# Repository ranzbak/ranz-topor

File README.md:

# topor — topological curved-trace router for KiCad

topor routes PCB connections as smooth, taut traces (straight segments joined by tangent arcs),
using topological routing: first decide *which side of every obstacle* a wire passes, then pull
each wire tight. It respects KiCad's design rules and checks its output with KiCad's own DRC.

Engine in Rust (`engine/`), packaged as a Python wheel; KiCad 10 plugin in `plugin/` (IPC API);
test and benchmark harness in `harness/`. Linux only for now.

## Status (version 0.4.0, milestone M4b: the plugin)

| Works now, from inside KiCad 10 | Comes in 0.5.0 (milestone M4a: the engine) |
|---|---|
| **Topor: route** button: pre-flight findings (code, cause, fix), options, progress with Cancel, before/after preview, **Accept = one undo step for the routes** (plus one for the zone refill) / Reject = nothing changed | private-badge-b n/n routed, 0 router DRC, ≤ 10 min (now 148/n in 60 s) |
| Whole board or a selection (between / touching selected footprints); existing copper kept, or ripped and re-routed; locked copper respected | priorities used for routing order (`@N` markers, `topor_pN` net classes, `[nets] priority` — computed and reported now) |
| Self-documenting `topor.toml` per project, generated [reference](docs/user/configuration.md); every finding names the KiCad menu or the key to change | pad exit stubs for fine pitch, same-net T-junctions, via rules from the board setup, bounded via relaxation, layer costs |
| Result verified by `kicad-cli` DRC on a copy before you decide; report folder (report, preview, DRC, log) per run | engine-side `do_not_touch` / `ignore_pads` options (applied by the plugin's scope now) |
| eprom-to-kernal 27/27 and wiccon-2023 62/62 routed, `routing_new 0`, `unconnected 0` (headless, judged by `kicad-cli`) | eprom / wiccon not worse than now |

The plugin needs a live GUI test before the 0.4.0 gate closes:
[docs/user/gui-test-checklist.md](docs/user/gui-test-checklist.md). Known limits:
[operate.md → Limitations](docs/user/operate.md#limitations).

## Topological core (branch `topor-topo`, in development)

A new engine core, written after TopoR's approach: the board is projected into one triangulation of all pads,
holes, keepouts, copper graphics and the outline; every connection is searched there as a topological path
(which side of each obstacle it passes), its net growing as a tree (a connection may end on a pad or a branch
point of copper it joins, including through-pad junctions); layers are assigned afterwards (Polubasov's via
minimisation), then rip-up and reroute, via reduction, and finally the drawing pulls each wire taut and checks
it against KiCad's rules. Plane pads get a stub and a via into their pour before any of this, so the planner
routes around them (a pour that fills only the pad's own layers gets a track alone into the fill); a pad that
no stub can serve is joined to its net's copper by a signal connection instead; pour pieces the routed copper
cuts off are stitched back with island vias or pad stubs.

What works on this branch:

- graded social factors instead of hard thresholds, each with a weight in `topor.toml [factors]` and a line in
  the run report: via_squeeze, junction_angle, branch, blocks_pad, squeeze, congestion, ignored_rule, and more
  ([factor reference](docs/dev/factors.md));
- keepouts: track keepouts per layer, via keepouts on any copper layer (a through via spans them all), pour
  keepouts in the fill estimate; copper graphics are obstacles on their layer;
- pour-island stitching after routing, and KiCad's minimum connection width respected by vias and stubs;
- layer-aware crossings: the search knows the layers each crossed trace is held to and does not cross where
  no layer assignment can separate the two (`[search] crossing_vias = "via"` also prices the implied via;
  off by default, the crossing factor stands for it);
- net-tree junctions in the layer assignment (two layers): a T junction is one layer domain (Polubasov's tee
  rule: two arms on one layer, the via on the third), and a via next to a junction stands at the junction;
  the junction angle price follows the Steiner-tree length bound (`junction_angle`, ψ curve, 0 from 120°);
- fuse after drawing: a trace that leaves a branch point or a pad right beside another trace of its net
  starts on that trace's copper where the two part (one copper, a T there), when that is cheaper by length
  and junction angle (and, in the octilinear style, by the drawing's own bend and any-angle prices: the link
  is an elbow or Z at 0/45/90 degrees where it fits) and keeps every clearance (`[search] fuse_branches`, on
  by default);
- the drawing's exact path has no out-and-back track pieces at its joints any more.

The board ladder at commit `121e3eb` (headless, `tools/route_board.sh`, judged by `kicad-cli` DRC after a zone
refill; "unconnected" counts DRC unconnected items, the hand-routed board's own count in brackets).
`private-badge-b` in this and the tables below is a 2-layer badge (a few hundred connections, written n, USB-C, arcs) whose design files
are not public; its rows stay as measurements, the public stand-in for new runs is esp-rust-board:

| Board | Routed | Unconnected (hand) | New routing DRC errors | Vias |
|---|---|---|---|---|
| eprom-to-kernal | 27/27 | 0 (0) | 0 | 0 |
| wiccon-2023 | 60/60 | 0 (0) | 0 | 23 |
| private-badge-b | 189/n | 47 (4) | 0 | 116 |
| qmtech | 346/426 | 85 (0) | 0 | 195 |

### The topological core inside KiCad (K1)

The **Topor: route** button runs this core in KiCad 10: pre-flight findings (pads inside track keepouts), a progress dialog that names the stage and round and shows router time and
total time (`[run] timeout_s` is now 600 s, an emergency stop; the `[optimize]` work caps end a run), Cancel at any
time, a preview with the open ratsnest in blue and a yellow dot at each rule violation the engine reports (while the loop runs, smaller dots at the plan's predicted errors), findings after routing (unrouted connections by reason, pour
islands and stitches, via squeeze, necking, ignored rules, ...; [operate.md](docs/user/operate.md#findings-after-routing)),
Accept (routes = one undo step, zone refill = a second). Every `topor.toml` setting the core reads reaches it (before K1 the `[optimize]`,
`[factors]` and the other core settings were dropped as "since 0.5.0"); settings of the classic engine say so in
the [reference](docs/user/configuration.md).

Live test, automated: `tools/gui_e2e.sh <board> <out_dir> --from-hand [--harness <metrics.json>]` drives KiCad 10
on a nested X display (Xephyr) with a separate KiCad home, never yours, opens a copy of the hand-routed board,
routes with *Rip up and re-route*, accepts, checks one Ctrl+Z restores the board, saves and judges the result with
KiCad's DRC ([gui-test-checklist.md](docs/user/gui-test-checklist.md#automated-run)). Plugin in KiCad vs the
headless harness on the same board (engine at K1):

| Board | Live plugin: routed / unconnected / routing_new / vias | Harness | Same? |
|---|---|---|---|
| wiccon-2023 | 60/60 / 0 / 0 / 23 | 60/60 / 0 / 0 / 23 | yes |
| private-badge-b | 184/n / 52 / 0 / 110 | 189/n / 47 / 0 / 116 | no: the copper-graphics polygons differ by < 0.5 µm (both contain KiCad's copper); the plugin's engine input with the harness's polygons routes 189/116 |
| qmtech | 349/426 / 84 / 0 / 206 | 346/426 / 85 / 0 / 195 | no: the net numbering differs (KiCad's API has no net codes, the plugin numbers nets by sorted name); the plugin's engine input renumbered with pcbnew's codes routes 346/195 |

Every other part of the engine input is now identical between the plugin and the harness (rules, widths, net
classes and priorities, pads, pours, zone connections, keepouts, teardrops); the remaining differences are the
router's sensitivity to the copper-graphics vertices and to the net numbering, not plugin errors. The ladder above
is unchanged by K1 (eprom 27/27, wiccon 60/60, private-badge-b 189/n, qmtech 346/426, routing_new 0).

### Iterations like TopoR: "Routes stable", OK, best of N runs (M-B0)

(Since M0 this whole-route cycle loop is `[optimize] loop = "cycles"`; the default is TopoR's loop on the topology,
see *Defaults = the TopoR method (M0)* below.) A run no longer stops after a fixed four rounds. Like TopoR it keeps iterating whole-route cycles: every cycle
routes the board again with the passages the drawing found too small lowered and with fluctuating factor weights
(Polubasov 2010) whose width starts wide, narrows every cycle and widens again when the run is stuck with
connections still open (annealing with reheating; `[optimize] fluctuation`, `fluctuation_narrowing`,
`fluctuation_stuck`, `fluctuation_reheat`). Every cycle's variants are pour-stitched and judged (a pour piece left
cut off counts as an error). When the best result gains less than `stable_gain_pct` over `stable_window` cycles the
routes are *stable* (TopoR 6.3 manual p. 73: "Autorouting may be stopped"; not before level 5–10): the progress
dialog says **Routes stable**; its two buttons stay **Accept** (stop and keep the best result so far, exactly the
board shown) and **Cancel** (stop at once, take nothing: the board stays as it was). With the dialog the run keeps
iterating for marginal gains until Accept / Cancel
(user 2026-11-16: "don't stop on stable"; `finish_when_stable = true` makes it finish at stable by itself,
`finish_patience`), and headless runs stop at stable. `[optimize] runs` (default 5) seeded runs go on in
parallel on the engine's threads and the best by the pick (errors, vias, length) is offered; `[optimize] rounds` (30) is only a
safety cap and `[run] timeout_s` (600 s) the emergency stop: runs on large boards (private-badge-b, qmtech with runs = 5) may hit it
and keep the best result so far (`TIME_BUDGET_HIT`).

Scorecard (KiCad DRC after a refill; connected % of KiCad's own input count, default run and median [range] of
seeds 1–5; `harness/scorecard.py`):

| Board | Before (fixed 4 rounds) | M-B0 (best of 5, until stable) | Router time before → after |
|---|---|---|---|
| eprom-to-kernal | 100 / 100 | 100 / 100 | 0.3 s → 2 s |
| wiccon-2023 | 100 / 100 [98.2–100] | 100 / 100 [100–100] | 1 s → 27 s |
| private-badge-b | 77.6 / 76.2 [74.3–78.6] | 80.5 / 79.5 [77.1–80.5] | 53 s → 442 s |
| qmtech | 79.6 / 78.9 [77.5–79.9] | 81.5 / 81.5 [80.6–83.2] | 174 s → 1014 s |

The defaults are provisional; their re-measurement with the M-B1 objective was skipped (user 2026-11-07: next
stage first).

Known limits: the complex boards (bornhack2026, hackerhotel2027, tanmatsu) are not on the ladder yet;
differential pairs are routed coupled but not length- or skew-tuned (D7, below); branching is not complete (the fuse moves copper after drawing but the
planner still reserves room for both traces; re-attaching after changes, junction relaxation toward the
Fermat point, vias as junctions and new branch points are open; the tee rule is two-layer only; a few
side-by-side pairs of one net remain, mostly at adjacent pins of one net and twin plane stubs); pour islands
are stitched afterwards, not prevented; results on the larger rungs move by a few connections with small
changes elsewhere on the board (rip-up order).

### Never drop (M-B1): violations instead of open connections

Like TopoR, a connection is no longer dropped when its drawing finds no legal geometry (a gap too narrow when
drawn, a via without a free site, a crossing that cannot be layered, a branch meeting its trace on another layer).
It stays in the router and is drawn anyway on its least violating geometry (the drawing's attempts, the exact path
with the clearance relaxed by the least amount that gives one, the funnels before the repair; a via goes to its
least violating site). Every rule it breaks is priced very high by the graded `violation` factor (1000 mm per
violation plus 1000 mm per 0.01 mm² of depth × length) and reported with its place, type and cause
(`VIOLATIONS` finding, `violations` in result.json). The best result counts errors first — connections with
violations plus connections without copper ("a design-rule violation cannot be compensated by any reduction of
wire length", Polubasov 2010) — then the least length + 25 mm per via + necking (`[optimize] pick = best`: necking = `neck_mm_per_mm2` x the copper drawn narrower than its net class width, in mm2, + `neck_via_mm` per via smaller than the class via; both defaults are guesses), then fewest shrinkages (`errors_weighted` = the old length + 25 mm per via without necking); "Routes stable" and the best of N see
the same count. The violating copper is written to the board; `[optimize] allow_violations = false` keeps the
legal-only output (such connections stay unrouted, as before). The topological core takes no DRC feedback, so the
plugin judges the result with one DRC round.

Scorecard at the defaults (best of 5 runs, measurement runs cut at 600 s of router time; default run and median
[range] of seeds 1–5; `harness/scorecard.py`, KiCad DRC after a refill):

| Board | Connected % M-B0 | Connected % M-B1 | Total length % of hand | Engine violations (connections) | Router time |
|---|---|---|---|---|---|
| eprom-to-kernal | 100 / 100 | 100 / 100 | 95 | 0 | 2 s |
| wiccon-2023 | 100 / 100 | 100 / 100 [100–100] | 89 / 88 | 0 | 24 s |
| private-badge-b | 80.5 / 79.5 [77.1–80.5] | 92.4 / 91.0 [90.0–91.4] | 62 / 63 | 236–385 (33–41) | 600 s (cut, all 6) |
| qmtech | 81.5 / 81.5 [80.6–83.2] | 91.4 / 91.6 [90.9–93.3] | 96 / 96 | 445–911 (47–58) | 600 s (cut, all 6) |

The violations are many and some are bad (copper over foreign pads and traces, `short` about half of them): the
drawing still realises a plan whose passages are too narrow or whose crossings are on one layer. Removing them
where they arise — the drawing failure fed back to the planner as a local cut, the crossing rules applied in the
topology — is the next stage (M-B2).

### Failures feed back locally; crossing rules in the planner (M-B2)

A cycle now feeds what went wrong back to the next one *where it happened*, and the planner removes the
crossing patterns that force violations while change is still cheap:

- **Local, fading history.** A violation puts history (a price for that connection only) on the passes of its
  trace near the place, weighted by the distance (1 on it, falling smoothly), not on the whole trace (Dr. CU,
  IEEE TCAD 2020, §IV-C: history only on "the intervals with violations"); a via without a site prices only the
  passages around its interval. Everything carried over fades by `[optimize] history_fade` (0.5) per cycle, and the
  present price of an over-full passage is kept level with the largest history so history cannot dominate
  (BoxRouter 2.0, p. 32:8–9). A passage the drawing found too narrow gets a lowered room (a cut, Haas 2026
  §VI-E); when a cycle comes out worse than the best, the cuts turn into a price (`[optimize] soft_cuts`). The
  drawing's rescue rips blocking traces by a graded price instead of a count, and the traces whose via count rose
  are rerouted first (Polubasov 2010).
- **Crossing rules** (`[optimize] crossing_rules`; `engine/src/topo/xrules.rs`): a trace of another net that wraps
  around a connection's terminal pad (a clinch or half-loop at a terminal, Luzin & Popov 2012 pp. 116–118 — the
  user's qmtech ADV7511 → U4 header case), two traces crossing twice (Luzin 2013 Fig. 16) and a crossing whose
  stretches are both held to one layer (Polubasov 2001) are re-planned pairwise — the terminal's trace first, the
  other one laid on the other side — before and after the rip-up, kept when the plan scores better. The planner's
  score counts crossings that cannot be layered as predicted violations.
- The `VIOLATIONS` finding groups what is left by origin: *pad exit* (a neighbour pin of the connection's own part —
  necking and pad exits, planned in M-C), via without a site, crossing, other copper in a narrow passage, static.

Scorecard (same setup as M-B1: best of 5 runs, cut at 600 s of router time; default / median [range] of seeds 1–5):

| Board | Connected % M-B1 | Connected % M-B2 | Engine violations M-B1 → M-B2 (connections) | shorts | Runs cut at 600 s |
|---|---|---|---|---|---|
| eprom-to-kernal | 100 / 100 | 100 / 100 | 0 → 0 | 0 | 0 / 6 |
| wiccon-2023 | 100 / 100 | 100 / 100 [100–100] | 0 → 0 | 0 | 0 / 6 |
| private-badge-b | 92.4 / 91.0 [90.0–91.4] | 90.0 / 91.0 [90.5–92.4] | 236–385 (29–38) → 95–176 (21–25) | 108–177 → 25–74 | 6 → 0 / 6 |
| qmtech | 91.4 / 91.6 [90.9–93.3] | 91.8 / 91.8 [91.1–92.6] | 445–911 (49–58) → 139–280 (32–40) | 234–613 → 35–154 | 6 → 6 / 6 |

Per cycle the errors now fall over the first cycles (median over all runs, private-badge-b 56.5 → 49 → 47.5 → 45;
qmtech 94 → 77.5 → 80.5 → 77 → 75); before, the violations of the later cycles grew (private-badge-b median 240 → 446).
On private-badge-b the default run's 5 more unconnected items are GND pour joins after the refill (stub and zone
pieces), not signal connections: the engine routes 222 of n in every run. On qmtech about 40 % of what is left
is at pad exits (M-C). Still open: the crossing rules leave traces of net trees with branch points alone, and a
trace drawn by force can still run over other copper for a millimetre or two.

### Widths, pad exits and via room decided in the plan (M-C)

The planner now decides what the drawing used to find out the hard way (TopoR's way: decide while change is cheap):

- **Pad exits.** A trace next to its own pad needs half its width plus the clearance to the next pin (the drawing's
  packer model); before, the one-plane routing counted no room at all there and planned exits through the 0.2 mm
  gap between fine-pitch pins, which the drawing then clipped (engine test `topo_mc`).
- **Width in the one-plane routing.** Every pass carries a width: the net width, or the minimum width (KiCad minimum
  track width / custom-rule minimum) where the passage is a bottleneck or the pad exit is too tight (TopoR 6.3
  manual p. 56: the minimum width "in bottlenecks unless a different path is available or near pads that are
  narrower than the wire"). A narrowed stretch runs from the nearest pad up to the bottleneck (`[search]
  neck_from_pad`), the search pays the graded *necking* factor once per stretch (TopoR 6.3 pp. 72–73: shrinkages
  are a criterion), and the layer assignment, rip-up and drawing pack the planned widths. The drawing draws the
  full width where it fits and the planned minimum only inside the planned stretches; it no longer narrows on its
  own (the option `[search] neck_in_drawing` was removed in M6, 2026-11-18).
- **Via room.** A via the plan puts at a layer change takes its spot: another net's via planned in the same small
  triangle has no site, so layer assignment and rip-up move it or reroute its trace (`[vias] reserve_sites`;
  Polubasov 2001 via intervals).

Scorecard (same setup as M-B2; default / median [range] of seeds 1–5; violations = the engine's report):

| Board | Connected % M-B2 | Connected % M-C | Connections with violations M-B2 → M-C | at a pad exit (connections) | KiCad DRC new | Runs cut at 600 s |
|---|---|---|---|---|---|---|
| eprom-to-kernal | 100 / 100 | 100 / 100 | 0 → 0 | 0 → 0 | 0 | 0 / 6 |
| wiccon-2023 | 100 / 100 | 100 / 100 | 0 → 0 | 0 → 0 | 0 | 0 / 6 |
| private-badge-b | 90.0 / 91.0 [90.5–92.4] | 90.5 / 90.0 [89.0–91.0] | 21–25 → 19–23 | 12–15 → 6–14 | 250–525 → 228–596 | 0 → 1 / 6 |
| qmtech | 91.8 / 91.8 [91.1–92.6] | 91.4 / 91.8 [91.4–92.1] | 32–40 → 13–23 | 23–33 → 7–15 | 516–817 → 149–496 | 6 → 6 / 6 |

On qmtech the ADV7511 → FPGA header traces now leave their pins straight out (pins 57–68 without a clip in the
default run). Still open: traces from neighbouring 0.5 mm pins that all turn to 45° right at the row's tips run
closer than their clearance allows (the planner compares passes edge by edge; mechfix `fx_fine_pitch_exit`, xfail),
a via inside a pin ring (qmtech ADV_DVDD → C22 under the chip) is not preferred yet (the connection routes legally
with its via outside the ring), and private-badge-b's GND pour joins after the refill still vary with the copper.

### Octilinear drawing: straight and 45 degrees (M-45)

The drawing now has a style (`[drawing] style`, default `"octilinear"`; `"smooth"` keeps the taut any-angle path):

- **Octilinear shape in the wire's corridor** (`engine/src/topo/octi.rs`). The legal taut path (TopoR's minimum-length
  wire, Popov & Popov 2012 pp. 117–122) is redrawn with 0/45/90 degree segments by a shortest path over nodes with 8
  ports and a price per bend that grows with its angle (Bast, Brosi & Storandt 2020, §2.1 p. 3: bend costs per angle,
  §4 p. 6: paths routed one after another, earlier ones are obstacles). The nodes are the taut path's vertices and the
  vertices of the *octagons* around nearby corners (the clearance circle's circumscribed octagon, edges at 0/45/90),
  so a trace that passes a pad or another trace runs parallel to it at the clearance. Few bends (`bend_mm` per 45
  degrees, a short piece between two bends pays more: `bend_spacing_mm`), an elongated pad is left along its axis
  until past its tip, and a trace follows a trace drawn beside it (`bundle_pull`), so bundles keep their pitch
  through their bends (the report's *bundles* line gives the skew: 2 × distance × tan 22.5° = 0.83 × pitch per 45°
  bend). The trace stays in its own lane on every passage it crosses (the room the plan gave the traces not drawn
  yet is kept) and the checker has the last word; else the taut run stays.
- **45 degrees is a cost, not a law.** Where 0/45/90 does not fit (a passage at another angle, just wide enough),
  that piece of the taut path keeps its angle and pays the `any_angle` factor (15 mm per stretch + 2 per mm), a bend
  sharper than 90 degrees pays `acute_bend` (50 mm, up to twice); each is a warning with place and angle
  (`[drawing] any_angle` / `acute` = `"forbidden"` to refuse them). The style never opens a connection or adds a
  violation: a trace drawn by force (never drop) keeps its least violating shape unless an octilinear one costs no
  more.
- **The planner knows the style** (`[drawing] octilinear_room`): the packer that P3/P4 and the drawing share counts
  the room an octilinear trace takes in a passage (`demand::octi_stretch`: the octagon around a wrapped corner, up
  to 1/cos 22.5° = 1.08 of the arc; the 0 and 45 degree legs of a slanted stretch at their own crossing angles).
- TopoR itself routes at any angle in automatic mode and offers 45 degrees only as a snap in manual editing (TopoR
  6.3 manual, PDF p. 238 FAQ and pp. 124–125); its "calculate wire shapes" step chooses arcs or straight lines
  (PDF p. 83).

Mechanism fixtures (`harness/mechfix.py`, all failing on the M-C engine): `fx_octi_straight`, `fx_octi_bend`,
`fx_octi_bundle`, `fx_octi_no_fit`, and `fx_fine_pitch_exit` (open since M-C: neighbouring 0.5 mm pins turning at
the row's tips; now they leave along the pin axis and stagger their bends).

Measurement with the standard runner (`harness/score_runs.py`: CPU-time limit 2400 s, 4 threads, one run at a time,
default run + seeds 1–5, M-C and M-45 interleaved; `scratch/ab-cpu/`). Default / median [range] of seeds 1–5; new DRC
= KiCad DRC violations in the new copper, per run:

| Board | Connected % M-C | Connected % M-45 | New DRC M-C | New DRC M-45 | Unconnected M-C → M-45 | CPU s (median) M-C → M-45 |
|---|---|---|---|---|---|---|
| eprom-to-kernal | 100 / 100 | 100 / 100 | 0 | 0 | 0 → 0 | 6 → 7 |
| wiccon-2023 | 100 / 100 | 100 / 100 | 0 | 0 | 0 → 0 | 62 → 93 |
| private-badge-b | 90.5 / 90.0 [89.0–91.0] | 93.8 / 91.0 [91.0–92.4] | 228–596 (median 327) | 90–380 (median 193) | 19–23 → 13–19 | 1405 → 1490 |
| qmtech | 91.4 / 91.6 [91.1–91.8] | 91.6 / 91.8 [91.6–92.1] | 149–496 (median 286) | 263–440 (median 327) | 34–37 → 33–35 | 2423 → 2426 (limit hit 5 of 6 → 6 of 6) |

private-badge-b gains (fewer violations and open connections). qmtech hits the CPU limit on every run, and octilinear
drawing costs about 50 % more CPU (wiccon), so fewer optimisation cycles fit in the budget; its violations against
other routed copper rose (`foreign_copper` 10–59 → 48–87 per run): the octilinear shapes take more of the passages
than the taut chords did. The structural answer (exact per-layer cut test and inflation, `docs/dev/inflated-sketch.md`)
is the next stage. The last qmtech runs of both sides ran under a load average of 10–16 (other work on the machine),
which costs work per CPU second.

### Differential pairs (D7)

Pairs are found by KiCad's own rule (`MatchDpSuffix` on the full net name, `toporlib/diffpair.py`, the one definition
the plugin hands to the engine) with KiCad's sizes: net class DP width / gap or a custom rule `diff_pair_gap`, floored
by the board minimums; via gap as KiCad's `EffectiveDiffPairViaGap`. Reference: [docs/dev/kicad-diff-pairs.md](docs/dev/kicad-diff-pairs.md).

- **Planned as one wide wire** (plan "Diff pairs = a wide wire"): the P connection carries the N connection, width
  `w + p / cos 22.5` (`p = w + gap`: both tracks, the gap and the room of a 45-degree mitre), so the demand model, the
  crossing graph, the layer assignment and the order (by width, early) see one wire; the N tree mirrors the P tree
  on partner pads. The planner works on an alias board in which the N copper carries the P net; partner pads with
  room between them get a P-net bridge there. The wire may neck to the single width at its pads: that is the
  fan-out zone (TopoR's movable split, 6.3 manual p. 171), priced by `necking`. A layer change is one via pair,
  checked as the disc around both vias.
- **Drawn as two tracks** at `+-p/2` about the drawn centre line (end legs moved onto the pad pairs' middle; 45-degree
  mitres in the octilinear style, mitred chords in smooth: there are no arcs in this core), joined to the pads by
  fan-out stubs that leave square to the pad pair first where needed (KiCad's pad gateways); each track zips at the
  nearest legal point, else the least violating one (never drop). P against N is checked against the pair gap
  (KiCad's `isCoupledDiffPair` clearance).
- **Polarity**: a connection pair whose pads swap sides is routed as two single tracks (qmtech USB_C_D, private-badge-b
  USB-C A/B rows); a coupled wire that arrives at its end pad pair from the side that swaps P and N is drawn and
  priced (`dp_polarity_cross`, the checker's violations): the planner does not choose the approach side yet.
- **Report and factors**: one line per pair connection (lengths, skew and the bend estimate, coupled share at the gap,
  uncoupled length at each end, vias), `result.json` `diff_pairs`, finding `DIFF_PAIRS`; graded factors
  `dp_uncoupled`, `dp_skew`, `dp_gap_deviation`, `dp_via_unpaired`, `dp_polarity_cross`; KiCad's violation wording
  only where a custom rule sets the limit. Settings: `[diffpair]` ([configuration.md](docs/user/configuration.md)).

Scorecard (`harness.score_runs`: cpu 2400 s, 4 threads, default run + seeds 1–5; KiCad DRC after refill; A = D7
@ a98d813, B = M-45 baseline `scratch/ab-cpu/m45`; `scratch/d7/score`):

| Board | Connected % default A / B | seeds A | seeds B | Routed by the engine A / B | Connections with violations A / B | CPU-limit hits A / B |
|---|---|---|---|---|---|---|
| eprom-to-kernal | 100 / 100 | 100 | 100 | 27 / 27 | 0 / 0 | 0 / 0 of 6 |
| wiccon-2023 | 100 / 100 | 100 | 100 | 60 / 60 | 0 / 0 | 0 / 0 of 6 |
| private-badge-b | 96.7 / 93.8 | 94.8 [91.9–96.7] | 91.0 [91.0–92.4] | 230 / 222 of n | 24–32 / 19–21 | 2 / 0 of 6 |
| qmtech | 95.7 / 91.6 | 95.7 [95.2–95.9] | 91.8 [91.6–92.1] | 426 / 400 of 426 | 29–37 / 22–26 | 6 / 6 of 6 |

All 26 qmtech and 8 private-badge-b pair connections are routed (before: skipped). qmtech HDMI pairs: coupled at the
gap 14–56 % per connection (median about 35 %), |skew| up to 1.25 mm (the fan-outs at U3 and the HDMI connector are
not symmetric; no tuning yet), no via; USB_C_D (pads swap sides) as two single tracks. 4–7 pair connections per run
carry violations, mostly at the HDMI connector, where a shield pin sits between P and N and the N fan-out crosses it,
and at private-badge-b U1 (pads 1.27 mm apart: the fan-out centred on the pad pair leaves the planned corridor) and U7
(the wire arrives from the side that swaps P and N: the planner does not choose the approach side yet). One qmtech
run (seed 4, first attempt) ended ENGINE_UNRESPONSIVE at the CPU limit under heavy machine load; its rerun is in the
table. eprom and wiccon have no pairs; their higher CPU seconds (11 vs 7, 142 vs 93) come from the busier machine.

### Defaults = the TopoR method (M0)

The TopoR pipeline (Polubasov 2010; TopoR 6.3 manual pp. 65, 72–73) is now what a run does by default, step by step:
the fixed board is triangulated once; every connection is laid once, widest first, never dropped (`[optimize]
initial = "once"`), its length priced as the shortest path that keeps the clearances (`[search] length = "taut"`);
layers are assigned by via minimisation with the per-edge room as the capacity price (`[capacity] model =
"edges"`, `edges_test = "price"`; the method's per-layer cut test, `model = "cuts"`, is an option for now: on a
large board its prices take the whole time limit before TopoR's loop starts, user decision 2026-11-13); TopoR's loop then works on the topology only (`[optimize] loop = "topor"`: single-wire rip-up and reroute
with oscillating weights, layer re-optimisation, vias relocated between their crossings, crossing rules, an archive
of variants with restarts); the picked variant is drawn once, without drawing feedback (`[search] drawing_feedback`
only acts with `loop = "cycles"` since M6, 2026-11-18). Every judgement is one price (S = Σ weight × amount): an over-full passage, a crossing on one layer or a
trace through foreign copper is costly, never a refusal (the per-edge model's hard move tests and its lexicographic
P4 pick are `[capacity] edges_test = "refuse"`, an option). The routing before M0 is still there, value for value:
`loop = "cycles"`, `initial = "per_cycle"`, `length = "even"`, `[capacity] model = "edges"`, `edges_test = "refuse"`
(`drawing_feedback = "auto"` is on with the cycles loop).

The drawing is still sequential (each wire an obstacle for the next) until the draw-once stages land; the stage
order from here (method first, then symptoms): M1 predicted-vs-drawn report → M2 draw once → M3 radii, spokes and
octilinear bands → M4 diff pairs in the topology → M5 defaults re-check → M6 remove firefighting → M7 necks and pad
exits → M8 install → M9 re-check the parked board symptoms.

## Requirements

- Linux (x86_64), **KiCad 10.0** with `kicad-cli` (tested 10.0.8)
- **Python ≥ 3.11** as KiCad's plugin interpreter (normally `/usr/bin/python3`), with the system wxPython 4.2
- Rust toolchain (stable, tested 1.96) — <https://rustup.rs> — to build the engine wheel
- For development: the system `pcbnew` Python module (harness and tests only, never the plugin)

## User guide

1. [Install](docs/user/install.md) — build, install into KiCad, enable the KiCad API, plugin environment.
2. [Operate](docs/user/operate.md) — first run, findings, options, scope by selection, progress, preview,
   Accept / Reject / undo, report folder, priorities, limitations.
3. [Configuration reference](docs/user/configuration.md) — every `topor.toml` key (generated).
4. [Troubleshooting](docs/user/troubleshoot.md) — one section per message code, exit codes, install problems.
5. [GUI test checklist](docs/user/gui-test-checklist.md) — the manual acceptance test in KiCad.

## Quick start

```bash
git clone git@github.com:ranzbak/ranz-topor.git topor && cd topor
tools/dev-venv.sh          # creates .venv (maturin, pytest; sees the system pcbnew)
tools/build.sh             # builds the engine wheel and installs the plugin into KiCad
```

Then KiCad → **Preferences → Plugins** → tick **Enable KiCad API**, open a **copy** of a board in the PCB
Editor (KiCad creates the plugin environment the first time) and click **Topor: route**. Details:
[install.md](docs/user/install.md).

## Route a board from the command line

The harness never touches your project: it routes a **snapshot copy**.

```bash
# 1. snapshot the source boards listed in harness/paths.py into scratch/boards/<board>/<sha12>/
.venv/bin/python -m harness.snapshot
# 2. rip the copy's tracks, route it with topor, run KiCad DRC, write metrics + images
.venv/bin/python -m harness.bench eprom-to-kernal /tmp/topor-run --router topor --threads 4
```

The output directory holds the routed board in `<board>-work/<board>.kicad_pcb` (open it in KiCad to
inspect), DRC json files (original, ripped, routed), `<board>--metrics.json` (routed, vias, length,
detours, DRC) and comparison PNGs (hand vs topor). More tools (engine probes, headless plugin runs,
reproducing a plugin run): [docs/dev/debug.md](docs/dev/debug.md).

The plugin's own run flow, headless, on a board copy:

```bash
tools/route_board.sh <board|pcb> <out_dir> [--timeout S] [--set section.key=value]
```

It strips the copy's tracks, routes it, runs KiCad DRC after a zone refill and writes `<name>--metrics.json` and
`<name>-compare.png`: the hand-routed board left, topor right, each with its open ratsnest (KiCad's DRC
unconnected items) drawn in blue. Details: [docs/dev/route-board.md](docs/dev/route-board.md).

## Development

[CONTRIBUTING.md](CONTRIBUTING.md): layout, build, tests, read-only boards, configuration and message
catalogues, commit style. Benchmarks and progress images are generated locally into `docs/benchmarks/`
(`harness.bench`, `harness.progress`; not in git) — key numbers are quoted in `docs/progress/STATE.md`.
Design and research library: [docs/](docs/README.md).

Routing mechanisms found on the ladder boards get a tiny synthetic regression layout each
(`harness/mechfix.py`, one function per mechanism, built with pcbnew in seconds), routed end to end with
KiCad DRC by `tests/test_mechfix.py`; they carry the `mechfix` marker and are not in the default run.

```bash
.venv/bin/pytest                                   # unit + integration (default)
.venv/bin/pytest tests/test_mechfix.py -m mechfix  # mechanism layouts, end to end (~2 min)
.venv/bin/pytest tests/gate -m "gate or not gate"  # milestone gates (~10 min)
.venv/bin/pytest tests/scaling -m scaling          # complexity/scaling budget
(cd engine && cargo test --release && cargo clippy --all-targets -- -D warnings)
```

## Repository layout

| Path | What |
|---|---|
| `engine/` | Rust engine: geometry kernel, triangulation, topological search, negotiation, smoothing, checker |
| `plugin/` | KiCad IPC plugin: `plugin.json`, entry point, `topor/` package (flow, dialogs, pre-flight, config), `wheels/`, `requirements.txt` |
| `toporlib/` | pure-Python code shared by plugin and harness (DRC, rules, DRC loop, board-file edits) |
| `harness/` | dev/test only: board snapshot/copy, rip, model export, rules, writer, DRC, render, bench |
| `tools/` | `build.sh`, `dev-venv.sh`, `bench.sh`, `render.sh` |
| `tests/` | pytest suites (unit, `plugin/`, `gate/`, `scaling/`) |
| `docs/` | user guide, developer guide, research library, design, plans, progress notes, benchmarks |

## License

topor is free software, licensed under the **GNU General Public License, version 3 only**
(SPDX: `GPL-3.0-only`); see [LICENSE](LICENSE).
Copyright (C) 2026 Paul Honig and contributors. Code from other GPL routers that allow "version 3 or
later", such as the gEDA PCB toporouter (GPL-2.0-or-later), may be reused under this license; keep their
copyright notices when doing so. GPL-2.0-only code cannot be combined with it.

### No warranty

This program is free software; you can redistribute it and/or modify it under the terms of the GNU
General Public License version 3 as published by the Free Software Foundation.

This program is distributed in the hope that it will be useful, but **WITHOUT ANY WARRANTY**; without
even the implied warranty of **MERCHANTABILITY** or **FITNESS FOR A PARTICULAR PURPOSE**. See the GNU
General Public License for more details (sections 15 and 16 of [LICENSE](LICENSE)).

You should have received a copy of the GNU General Public License along with this program; if not, see
<https://www.gnu.org/licenses/>.

In particular: the copper topor produces is not guaranteed to be correct, complete or manufacturable.
Check every routed board with KiCad's DRC and your own review before you send it to a fab.

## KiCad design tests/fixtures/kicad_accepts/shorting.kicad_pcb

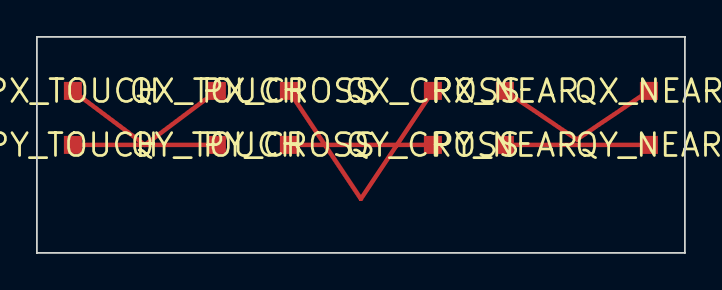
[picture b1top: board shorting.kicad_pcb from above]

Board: 2 copper layers, 36.0 x 12.0 mm, 12 parts (0 on the bottom side), 6 nets.

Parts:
PX_CROSS: PX_CROSS
PX_NEAR: PX_NEAR
PX_TOUCH: PX_TOUCH
PY_CROSS: PY_CROSS
PY_NEAR: PY_NEAR
PY_TOUCH: PY_TOUCH
QX_CROSS: QX_CROSS
QX_NEAR: QX_NEAR
QX_TOUCH: QX_TOUCH
QY_CROSS: QY_CROSS
QY_NEAR: QY_NEAR
QY_TOUCH: QY_TOUCH

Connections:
X_CROSS: PX_CROSS.1, QX_CROSS.1
X_NEAR: PX_NEAR.1, QX_NEAR.1
X_TOUCH: PX_TOUCH.1, QX_TOUCH.1
Y_CROSS: PY_CROSS.1, QY_CROSS.1
Y_NEAR: PY_NEAR.1, QY_NEAR.1
Y_TOUCH: PY_TOUCH.1, QY_TOUCH.1

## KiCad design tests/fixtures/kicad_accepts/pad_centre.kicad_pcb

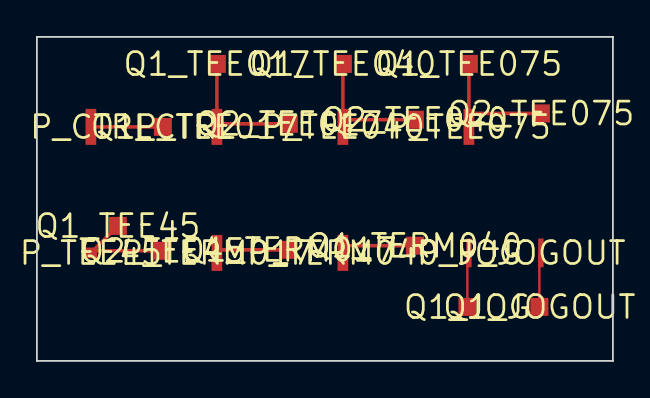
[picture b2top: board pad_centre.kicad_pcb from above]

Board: 2 copper layers, 32.0 x 18.0 mm, 22 parts (0 on the bottom side), 9 nets.

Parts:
P_CTRL: P_CTRL
P_JOG: P_JOG
P_JOGOUT: P_JOGOUT
P_TEE017: P_TEE017
P_TEE040: P_TEE040
P_TEE45: P_TEE45
P_TEE075: P_TEE075
P_TERM017: P_TERM017
P_TERM040: P_TERM040
Q1_CTRL: Q1_CTRL
Q1_JOG: Q1_JOG
Q1_JOGOUT: Q1_JOGOUT
Q1_TEE017: Q1_TEE017
Q1_TEE040: Q1_TEE040
Q1_TEE45: Q1_TEE45
Q1_TEE075: Q1_TEE075
Q1_TERM017: Q1_TERM017
Q1_TERM040: Q1_TERM040
Q2_TEE017: Q2_TEE017
Q2_TEE040: Q2_TEE040
Q2_TEE45: Q2_TEE45
Q2_TEE075: Q2_TEE075

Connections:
CTRL: P_CTRL.1, Q1_CTRL.1
JOG: P_JOG.1, Q1_JOG.1
JOGOUT: P_JOGOUT.1, Q1_JOGOUT.1
TEE017: P_TEE017.1, Q1_TEE017.1, Q2_TEE017.1
TEE040: P_TEE040.1, Q1_TEE040.1, Q2_TEE040.1
TEE45: P_TEE45.1, Q1_TEE45.1, Q2_TEE45.1
TEE075: P_TEE075.1, Q1_TEE075.1, Q2_TEE075.1
TERM017: P_TERM017.1, Q1_TERM017.1
TERM040: P_TERM040.1, Q1_TERM040.1

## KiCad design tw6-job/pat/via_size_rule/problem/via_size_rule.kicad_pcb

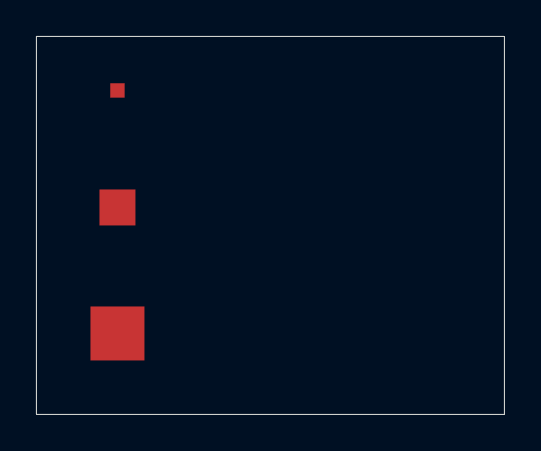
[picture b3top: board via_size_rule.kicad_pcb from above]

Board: 2 copper layers, 26.0 x 21.0 mm, 6 parts (0 on the bottom side), 3 nets, no tracks yet.

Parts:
HEAVY_1: HEAVY_1
HEAVY_2: HEAVY_2
PWR_1: PWR_1
PWR_2: PWR_2
SIG_1: SIG_1
SIG_2: SIG_2

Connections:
HEAVY: HEAVY_1.1, HEAVY_2.1
PWR: PWR_1.1, PWR_2.1
SIG: SIG_1.1, SIG_2.1

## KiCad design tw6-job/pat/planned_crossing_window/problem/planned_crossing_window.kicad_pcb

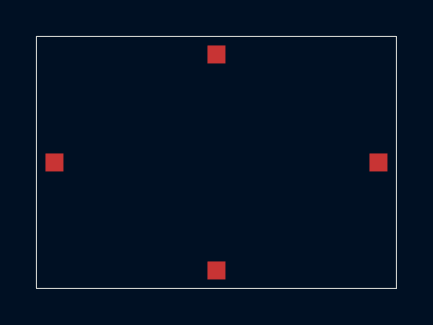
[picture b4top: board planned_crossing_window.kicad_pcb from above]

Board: 2 copper layers, 20.0 x 14.0 mm, 4 parts (0 on the bottom side), 2 nets, no tracks yet.

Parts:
J1: J1
J2: J2
J3: J3
J4: J4

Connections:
SDA: J3.1, J4.1
VCC: J1.1, J2.1
